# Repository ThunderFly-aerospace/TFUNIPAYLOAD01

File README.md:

# TFUNIPAYLOAD01 - universal interface for sensor payload 

Reference design of PX4 interface for generic [TF-ATMON](https://docs.thunderfly.cz/instruments/TF-ATMON) compatible payload. The purpose of this design is to connect a sensor to the [TF-ATMON](https://www.thunderfly.cz/tf-atmon.html) system, despite that the sensor does not have any driver in the flight stack (autopilot firmware), but at the same time, it is required for atmospheric measurement.

The sensor is connected to the TFUNIPAYLOAD board using a UART, I2C, GPIO, ADC, or SPI interface. 
ATmega in TFUNIPAYLOAD01 runs the Arduino firmware, which prepares [MAVLink](https://en.wikipedia.org/wiki/MAVLink) messages to be logged and transported to GCS running TF-ATMON infrastructure described in the block schematics. 

## Example of use

FMU firmware (PX4 or Ardupilot, for example) is capable of logging MAVLink data from the UART (Telemetry Port).  Therefore, the “UART Peripheral” connector on TFUNIPAYLOAD01 is intended for connecting a UART-based FMU using the Pixhawk DS-009 telemetry pinout. Typical devices include flight controllers (autopilot) or companion computers.

[Pixhawk standard connector pinout](https://github.com/pixhawk/Pixhawk-Standards/blob/master/DS-009%20Pixhawk%20Connector%20Standard.pdf) is as follows:

| Pin        | Signal | Voltage levels  | Read/Write | Write |
| ---------- |:------:| ---------------:|------|------|
| 1 (red)    | Vcc | +5V | Optional | Optional |
| 2 (blk)    | TX (OUT)  |   +3.3 V | PX4 -> Payload | -- |
| 3 (blk)    | RX (IN)   |   +3.3 V | Payload -> PX4 | Payload -> PX4 |
| 4 (blk)    | CTS (IN)  |   +3.3 V | -- | -- |
| 5 (blk)    | RTS (OUT) |   +3.3 V | -- | -- |
| 6 (blk)    | GND       |   GND    | GND | GND |

For data to be received by the PX4 autopilot, it must have a specific form. Explicitly, it needs to use a serial link with  [MAVLink v2](https://mavlink.io/en/) packets. In that case, the [Tunnel (#385)](https://mavlink.io/en/messages/common.html#TUNNEL) packets will be stored in the autopilot's log file and forwarded to the GCS. 
The [TFUSBSERIAL01](https://github.com/ThunderFly-aerospace/TFUSBSERIAL01) hardware could be used to easily check for correct wiring. 

The following library [c_library_v2](https://github.com/mavlink/c_library_v2), which is automatically generated from message definition files, could be used. 

## Firmware examples

There are multiple Arduino-based firmware examples for different use cases. 

#### TFUNIPAYLOAD

[TFUNIPAYLOAD.ino](/SW/arduino/src/TFUNIPAYLOAD/TFUNIPAYLOAD.ino) contains a basic example, which listens to MAVLink messages from the autopilot and sends tunnel packets with random data to the autopilot.

#### TFUNIPAYLOAD_MINIMAL

Since message parsing requires a lot of memory, we have prepared an example where only [HEARTBEAT](https://mavlink.io/en/messages/common.html#HEARTBEAT) and [TUNNEL](https://mavlink.io/en/messages/common.html#TUNNEL) messages are sent. This example does not require a connected TX (from autopilot), and it is, therefore, suitable for MCUs with less memory.

Source code: [TFUNIPAYLOAD_MINIMAL.ino](/SW/arduino/src/TFUNIPAYLOAD_MINIMAL/TFUNIPAYLOAD_MINIMAL.ino)

#### Tunnel packet sending function

[Tunnel packet sending function](https://github.com/ThunderFly-aerospace/TFUNIPAYLOAD/blob/79eee22fe32725179d1df2b6ca72e901e2be1834/SW/arduino/src/TFUNIPAYLOAD/TFUNIPAYLOAD.ino#L50) ```  mav.SendTunnelData(data, sizeof(data), 0, 1, 0); ``` is the main function that enables sending tunnel data to the autopilot. It takes the following as its arguments:
 * data in uint8_t [127] format
 * data length
 * data type (every type of logged data will have its ID - it serves for easy differentiation of different sensors
 * target sysid
 * target compid

If the data only needs to be logged, the target sysid and compid must match the autopilot’s address, which is usually `sysid: 1, compid: 1`. If the data has to be logged and sent to GCS, broadcast must be set: `sysid: 1, compid: 0` or better `sysid: 0, compid: 0`. 

The autopilot only has a limited amount of storage memory (SD card), and it is therefore necessary to ensure, on the payload’s side, that it does not fill up during the flight. Alternatively, a maximum bandwidth on the MAVLink interface can be set in the autopilot. It is not tested what happens when the level set is exceeded[2021/09]. 

## Autopilot configuration

In the autopilot’s PX4 firmware, it is necessary to correctly set the following parameters (MAV_1_FORWARD and others will be visible only after setting the parameter MAV_1_CONFIG and rebooting the PX4): 

|     Parametr    | Value | Description |
|-----------------|-----------|------|
| [MAV_1_CONFIG](http://docs.px4.io/main/en/advanced_config/parameter_reference.html#mavlink)    | TELEM 2   | The port on which MAVLink packets will be expected. Any free TELEM port can be set |
| [MAV_1_FORWARD](http://docs.px4.io/main/en/advanced_config/parameter_reference.html#mavlink)   | **1**     | Enable message forwarding from this port|
| [MAV_1_RADIO_CTL](http://docs.px4.io/main/en/advanced_config/parameter_reference.html#mavlink) | **0**     | |
| [MAV_1_RATE](http://docs.px4.io/main/en/advanced_config/parameter_reference.html#mavlink)      | **0 B/s** | |
| [SER_TEL2_BAUD](http://docs.px4.io/main/en/advanced_config/parameter_reference.html#serial)   |     57600 | It is necessary to configure the port that is set in `MAV_1_CONFIG` parameter. The setting of the baud rate port. |

How to set the parameters in PX4 is described in [manual](http://docs.px4.io/master/en/advanced_config/parameters.html#changing-a-parameter).

## How to check that the autopilot correctly receives MAVLink messages?

There are several options to find out whether the message sending is working correctly.

### Using the QGC

The message can be easily viewed live in [QGC](https://github.com/mavlink/qgroundcontrol/releases). For this procedure to function, two conditions must be fulfilled.

 1. The message must be broadcast, meaning the message must have set its target sysid and compid to 0, 0.
 2. The computer must be connected via a MAVLink instance that supports message forwarding (e.g., via TELEM1 port using modem or UART-USB converter); autopilot's USB does not support it.

 > Warning: this procedure will not work if the autopilot is connected via a USB cable to the Pixhawk's USB port.

After opening QGC, connect the autopilot to the computer (via RF modem or an external USB converter connected to the serial port). Once the autopilot is connected, live data (such as autopilot attitude) will become visible. A subsequent click on the QGC logo in the top left corner will open a menu where you select `Analyze tools` and then open `MAVLink inspector` in order to see a list of all messages. 

The list of messages, when functioning correctly, should contain TUNNEL messages. 

### Using the MAVLink PX4 console

An advantage of connecting via [PX4 console](https://docs.px4.io/main/en/debug/consoles.html) lies in its independence from broadcasting settings and the possibility of checking whether the message is received and parsed by the autopilot. If the message is visible here (and the logging is enabled), it is at the same time already logged. With this procedure, a USB cable connection to the autopilot can be used. 

Autopilot console can be entered using the following Python [script](https://github.com/ThunderFly-aerospace/PX4Firmware/blob/master/Tools/mavlink_shell.py) or using [QGC](https://github.com/mavlink/qgroundcontrol/releases).

 * In the case of using a Python script, it is enough to run the python3 script with a parameter of the chosen serial link to which the autopilot/modem is connected.
 * In the case of using QGC, the QGC must be opened in the autopilot console by clicking on the QGC logo (on the top), choosing `Analyze tools`, and choosing a console.

The received message can then be retrieved using the following command:

`listener mavlink_tunnel`

The command displays the current tunnel message. Adding the -n 100` parameter will cause a listing of 100 messages (and the new message will display by itself).

If the communication is working properly, the output should look like this:

### From a uLog file

The tunnel message can be logged into autopilot in a standard [uLog format](https://docs.px4.io/main/en/dev_log/ulog_file_format.html). However, because tools like [Flight review](https://review.px4.io/) are unable to display such data format, it is necessary to overcome this problem using a suitable tool. One option is using the [PlotJuggler](https://plotjuggler.io/). 
Another possibility for opening the log is the [Jupiter notebook](https://github.com/ThunderFly-aerospace/TFUNIPAYLOAD/blob/master/SW/LogViewer/ReadTunnelData.ipynb).

## Known limitations

  * Avoiding overloading the autopilot's memory with messages must be ensured on the payload side
  * A maximum of 2 devices + modem or 3 devices without a modem can be connected in this way. The limitation is caused by the MAVLink driver, which is only able to connect a maximum of 3 instances of MAVLink devices, and also due to the limited number of UART interfaces of the autopilot.
  * It is not possible for the input of payload messages and output to [sik modem](https://github.com/ThunderFly-aerospace/TFSIK01) to have the same type of MAVLink messages (stream) that would differ only in the number of messages per second. This means that it is not possible to simply select a data stream to be transmitted to the ground from the data stream intended for logging. If it is necessary to log more detailed data (with higher frequency) another MAVLink message must be logged.

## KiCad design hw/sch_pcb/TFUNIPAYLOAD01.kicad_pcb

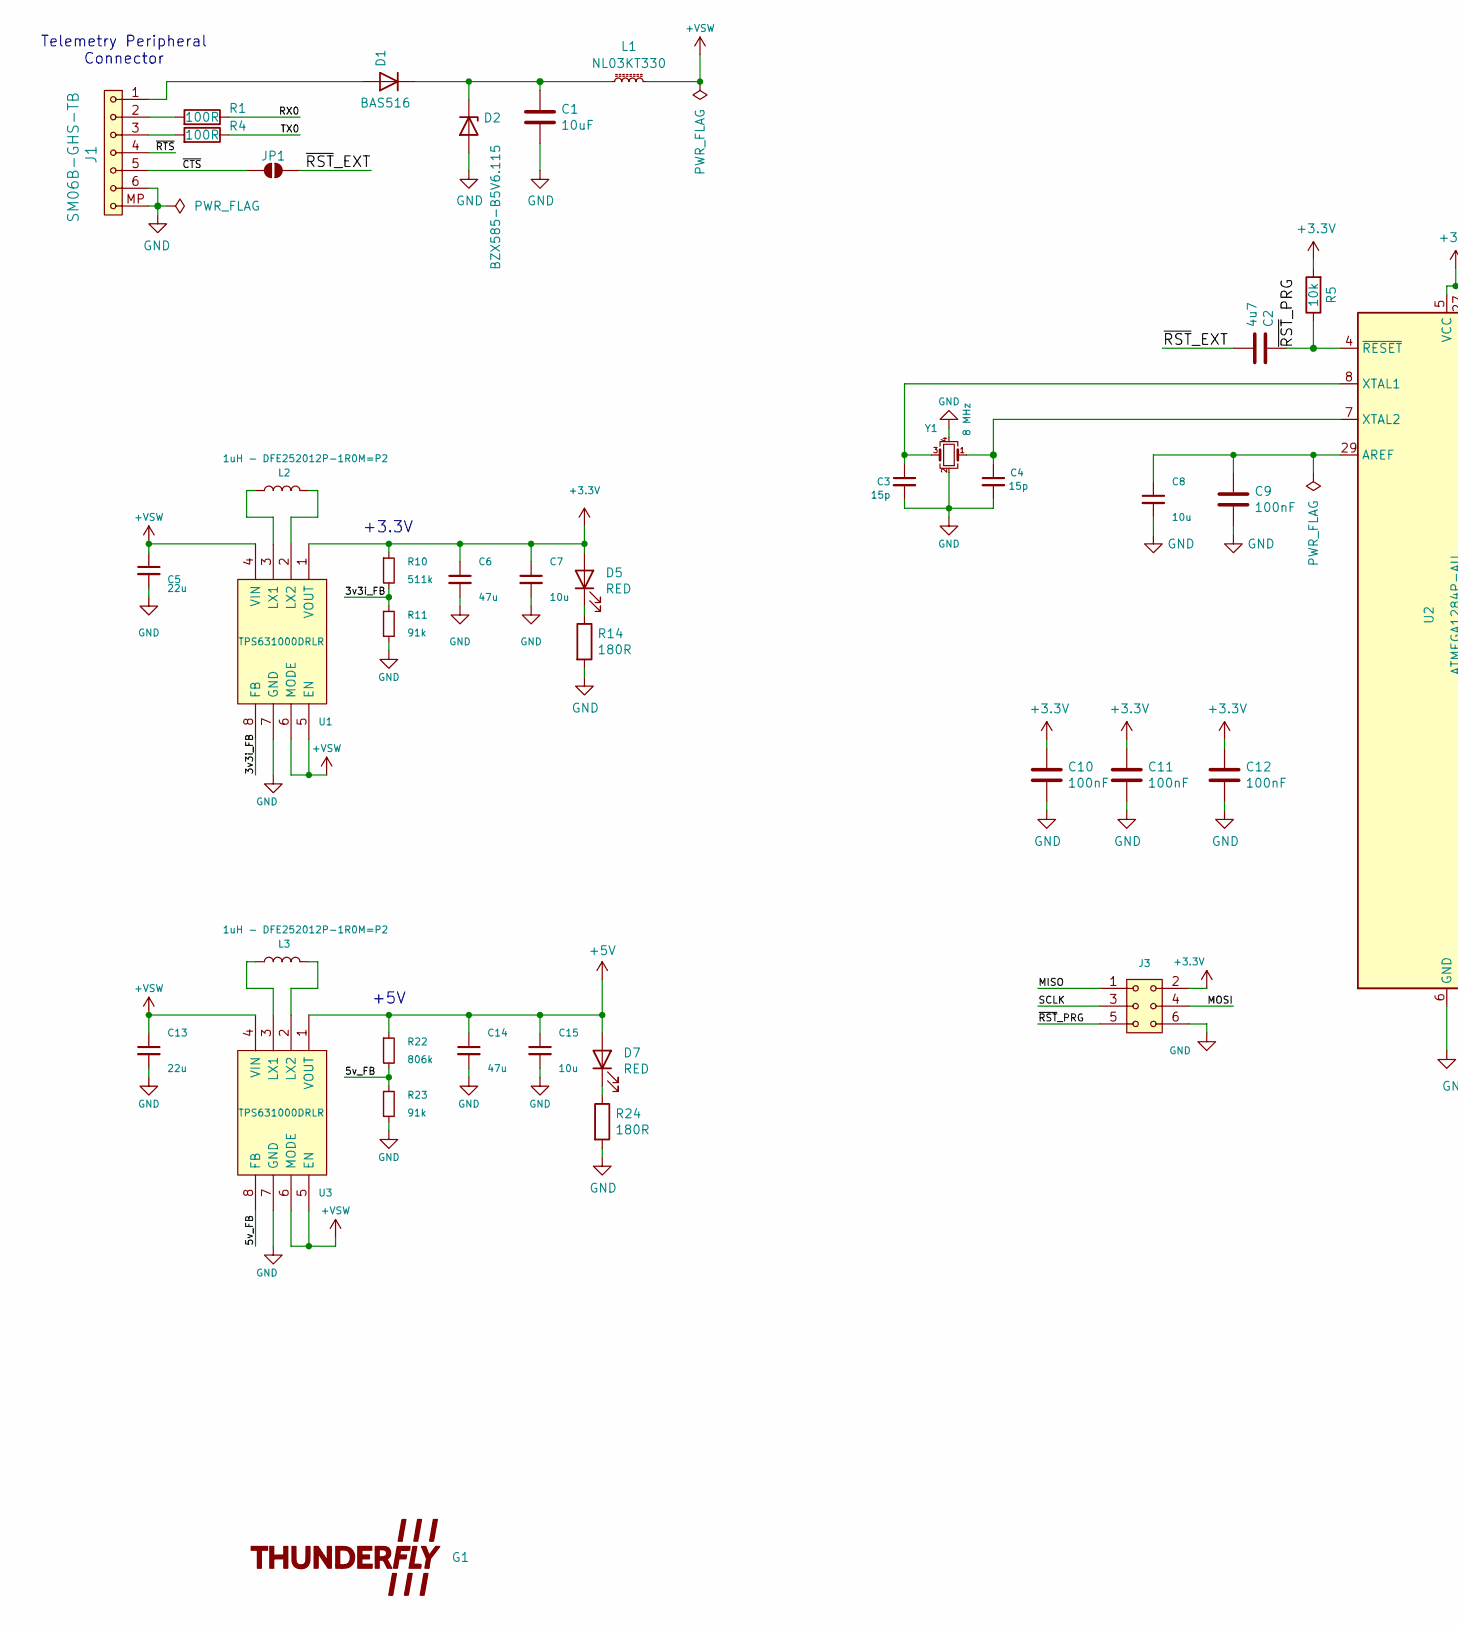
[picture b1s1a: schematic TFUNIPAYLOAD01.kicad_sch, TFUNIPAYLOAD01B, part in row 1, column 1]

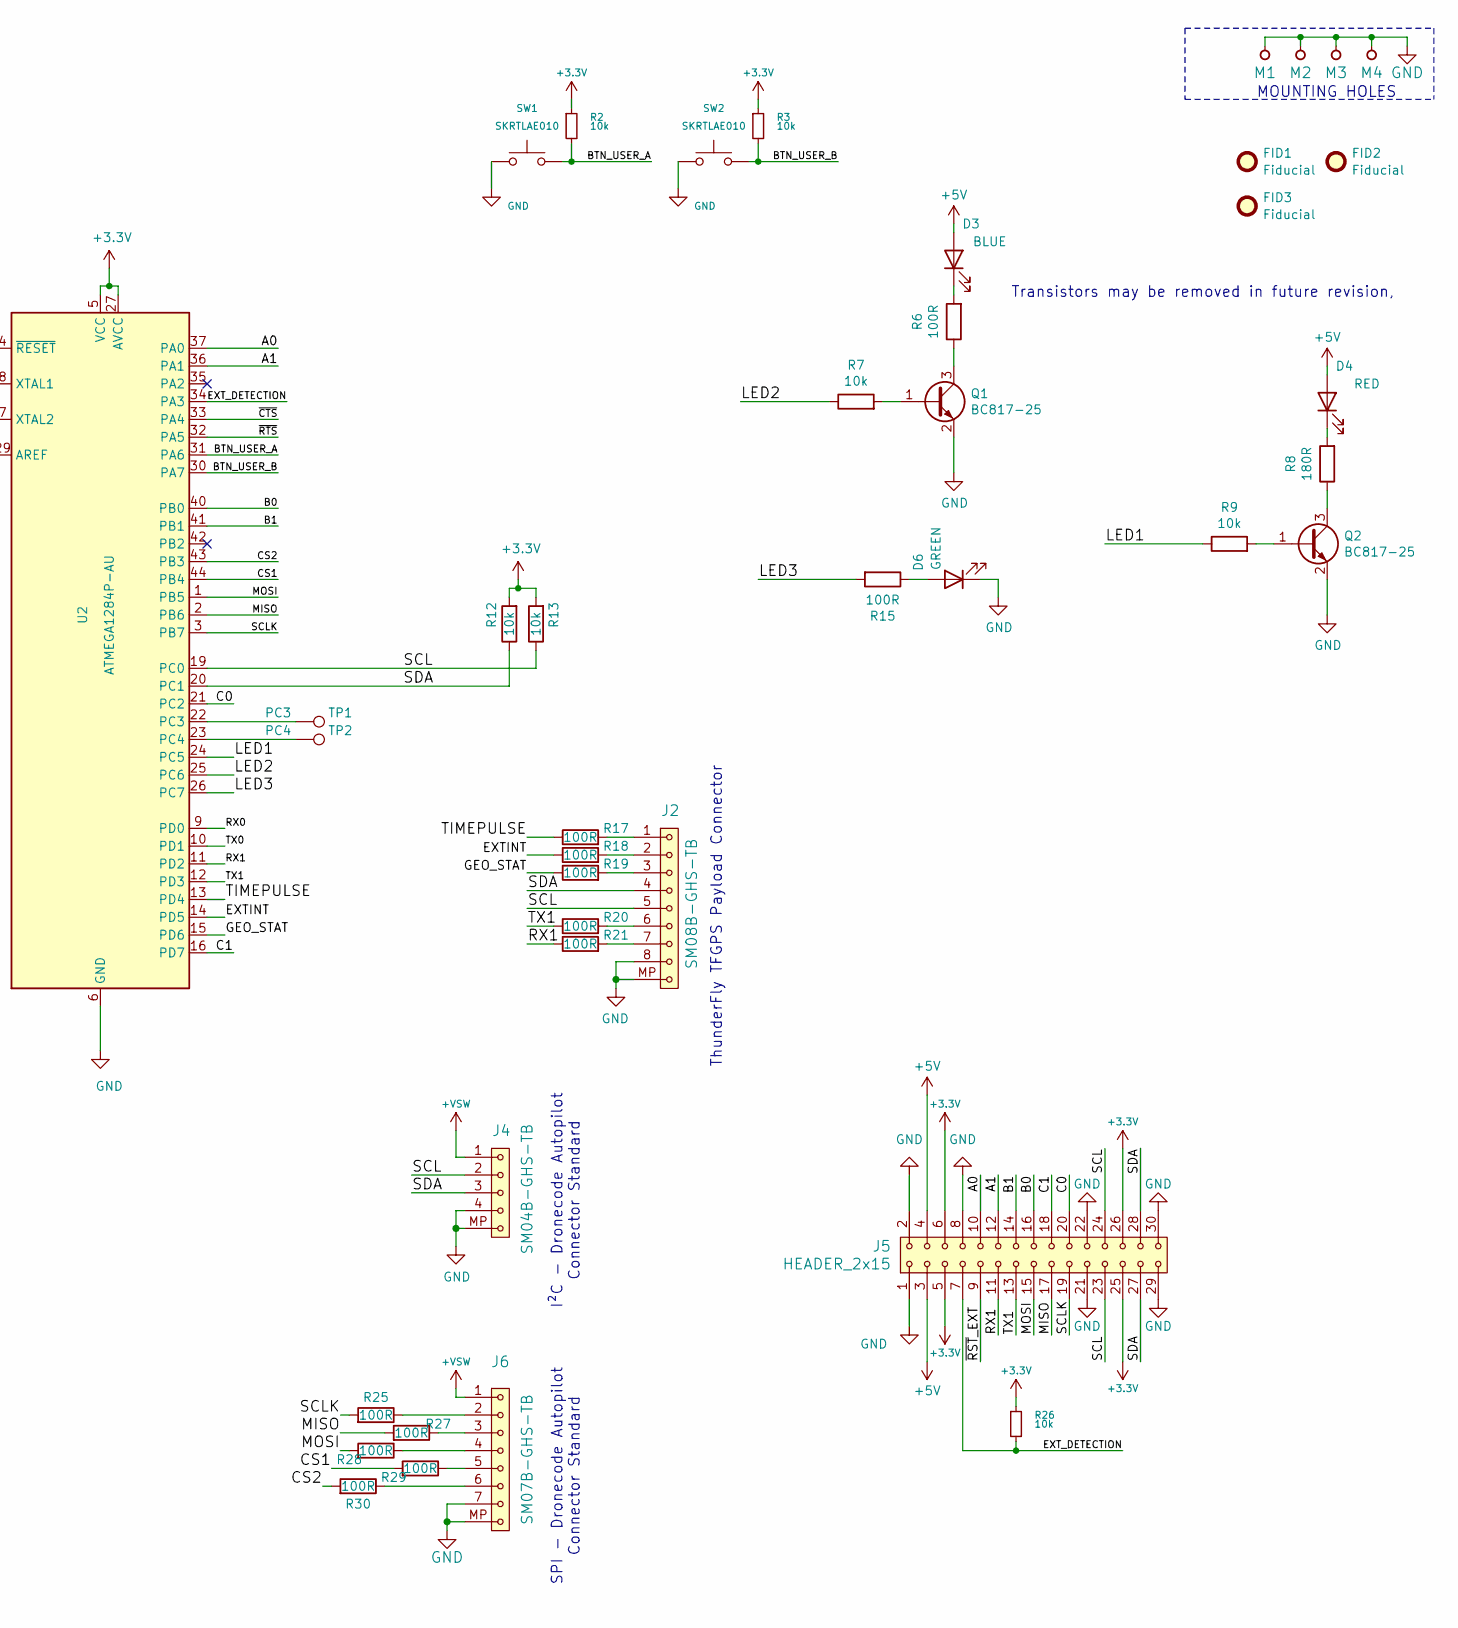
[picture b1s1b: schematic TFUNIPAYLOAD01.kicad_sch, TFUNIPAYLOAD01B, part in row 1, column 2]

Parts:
C1: 10uF; C_0805_2012Metric
C2: 4u7; C_0805_2012Metric
C3, C4: 15p; C_0805_2012Metric
C5, C13: 22u; C_0805_2012Metric
C6, C14: 47u; C_0805_2012Metric
C7, C8, C15: 10u; C_0805_2012Metric
C9, C10, C11, C12: 100nF; C_0805_2012Metric
D1: BAS516; D_SOD-523
D2: BZX585-B5V6.115; D_SOD-523
D3: BLUE; LED_1206_mill
D4, D5, D7: RED; LED_1206_mill
D6: GREEN; LED_1206_mill
FID1, FID2, FID3: Fiducial; Fiducial_1mm_Mask2mm
G1: LOGO; TF
J1: SM06B-GHS-TB; JST_GH_SM06B-GHS-TB_1x06-1MP_P1.25mm_Horizontal
J2: SM08B-GHS-TB; JST_GH_SM08B-GHS-TB_1x08-1MP_P1.25mm_Horizontal
J3: HEADER_2x03; SMD_2x03_WO_paste
J4: SM04B-GHS-TB; JST_GH_SM04B-GHS-TB_1x04-1MP_P1.25mm_Horizontal
J5: HEADER_2x15; Straight_2x15
J6: SM07B-GHS-TB; JST_GH_SM07B-GHS-TB_1x07-1MP_P1.25mm_Horizontal
JP1: SolderJumper_2_Open; SolderJumper-2_P1.3mm_Open_RoundedPad1.0x1.5mm
L1: NL03KT330; L_0603_1608Metric_Pad1.05x0.95mm_HandSolder
L2, L3: 1uH - DFE252012P-1R0M=P2; L_1008_2520Metric
M1, M2, M3, M4: HOLE; MountingHole_3mm
Q1, Q2: BC817-25; SOT-23
R1, R4, R6, R15, R17, R18, R19, R20, R21, R25, R27, R28, R29, R30: 100R; R_0805_2012Metric
R2, R3, R5, R7, R9, R12, R13, R26: 10k; R_0805_2012Metric
R8, R14, R24: 180R; R_0805_2012Metric
R10: 511k; R_0805_2012Metric
R11, R23: 91k; R_0805_2012Metric
R22: 806k; R_0805_2012Metric
SW1, SW2: SKRTLAE010; KMT031 NGJ LHS C&K
TP1: PC3; TestPoint_Pad_D1.0mm
TP2: PC4; TestPoint_Pad_D1.0mm
U1, U3: TPS631000DRLR; SOT-583-8; Mouser Part Number 595-TPS631000DRLR
U2: ATMEGA1284P-AU; TQFP-44_10x10mm_P0.8mm
Y1: 8 MHz; Crystal_SMD_3225-4Pin_3.2x2.5mm

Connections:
+3.3V: C6.1, C7.1, C10.1, C11.1, C12.1, D5.2 (A), J3.2, J5.5, J5.6, J5.25, J5.26, R2.1, R3.1, R5.2, R10.1, R12.2, R13.2, R26.1, U1.1 (VOUT), U2.5 (VCC), U2.17 (VCC), U2.27 (AVCC), U2.38 (VCC)
+5V: C14.1, C15.1, D3.2 (A), D4.2 (A), D7.2 (A), J5.3, J5.4, R22.1, U3.1 (VOUT)
+VSW: C5.1, C13.1, J4.1, J6.1, L1.2, U1.4 (VIN), U1.5 (EN), U1.6 (MODE), U3.4 (VIN), U3.5 (EN), U3.6 (MODE)
/3v3i_FB: R10.2, R11.1, U1.8 (FB)
/5v_FB: R22.2, R23.1, U3.8 (FB)
/A0: J5.10, U2.37 (PA0)
/A1: J5.12, U2.36 (PA1)
/B0: J5.16, U2.40 (PB0)
/B1: J5.14, U2.41 (PB1)
/BTN_USER_A: R2.2, SW1.1, U2.31 (PA6)
/BTN_USER_B: R3.2, SW2.1, U2.30 (PA7)
/C0: J5.20, U2.21 (PC2)
/C1: J5.18, U2.16 (PD7)
/CS1: R29.2, U2.44 (PB4)
/CS2: R30.2, U2.43 (PB3)
/EXTINT: R18.1, U2.14 (PD5)
/EXT_DETECTION: J5.7, R26.2, U2.34 (PA3)
/GEO_STAT: R19.1, U2.15 (PD6)
/LED1: R9.1, U2.24 (PC5)
/LED2: R7.1, U2.25 (PC6)
/LED3: R15.2, U2.26 (PC7)
/MISO: J3.1, J5.17, R27.2, U2.2 (PB6)
/MOSI: J3.4, J5.15, R28.2, U2.1 (PB5)
/RX0: R1.1, U2.9 (PD0)
/RX1: J5.11, R21.1, U2.11 (PD2)
/SCL: J2.5, J4.2, J5.23, J5.24, R13.1, U2.19 (PC0)
/SCLK: J3.3, J5.19, R25.2, U2.3 (PB7)
/SDA: J2.4, J4.3, J5.27, J5.28, R12.1, U2.20 (PC1)
/TIMEPULSE: R17.1, U2.13 (PD4)
/TX0: R4.1, U2.10 (PD1)
/TX1: J5.13, R20.1, U2.12 (PD3)
/~CTS: J1.5, JP1.2 (B), U2.33 (PA4)
/~RST_EXT: C2.2, J5.9, JP1.1 (A)
/~RST_PRG: C2.1, J3.5, R5.1, U2.4 (~RESET)
/~RTS: J1.4, U2.32 (PA5)
GND: C1.2, C3.2, C4.2, C5.2, C6.2, C7.2, C8.2, C9.2, C10.2, C11.2, C12.2, C13.2, C14.2, C15.2, D2.2 (A), D6.1 (K), J1.6, J1.MP, J2.8, J2.MP, J3.6, J4.4, J4.MP, J5.1, J5.2, J5.8, J5.21, J5.22, J5.29, J5.30, J6.7, J6.MP, M1.1, M2.1, M3.1, M4.1, Q1.2 (E), Q2.2 (E), R11.2, R14.2, R23.2, R24.2, SW1.2, SW2.2, U1.7 (GND), U2.6 (GND), U2.18 (GND), U2.28 (GND), U2.39 (GND), U3.7 (GND), Y1.2, Y1.4
unnamed: D1.2 (A), J1.1
unnamed: C1.1, D1.1 (K), D2.1 (K), L1.1
unnamed: D3.1 (K), R6.2
unnamed: D4.1 (K), R8.2
unnamed: D5.1 (K), R14.1
unnamed: D6.2 (A), R15.1
unnamed: D7.1 (K), R24.1
unnamed: J1.2, R1.2
unnamed: J1.3, R4.2
unnamed: J2.1, R17.2
unnamed: J2.2, R18.2
unnamed: J2.3, R19.2
unnamed: J2.6, R20.2
unnamed: J2.7, R21.2
unnamed: J6.2, R25.1
unnamed: J6.3, R27.1
unnamed: J6.4, R28.1
unnamed: J6.5, R29.1
unnamed: J6.6, R30.1
unnamed: Q1.1 (B), R7.2
unnamed: Q1.3 (C), R6.1
unnamed: Q2.1 (B), R9.2
unnamed: Q2.3 (C), R8.1
unnamed: L2.1, U1.3 (LX1)
unnamed: L2.2, U1.2 (LX2)
unnamed: C8.1, C9.1, U2.29 (AREF)
unnamed: TP1.1, U2.22 (PC3)
unnamed: TP2.1, U2.23 (PC4)
unnamed: C3.1, U2.8 (XTAL1), Y1.3
unnamed: C4.1, U2.7 (XTAL2), Y1.1
unnamed: L3.1, U3.3 (LX1)
unnamed: L3.2, U3.2 (LX2)

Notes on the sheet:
I²C - Dronecode Autopilot Connector Standard
Transistors may be removed in future revision,
SPI - Dronecode Autopilot Connector Standard
ThunderFly TFGPS Payload Connector
Telemetry Peripheral Connector
+5V
+3.3V
MOUNTING HOLES

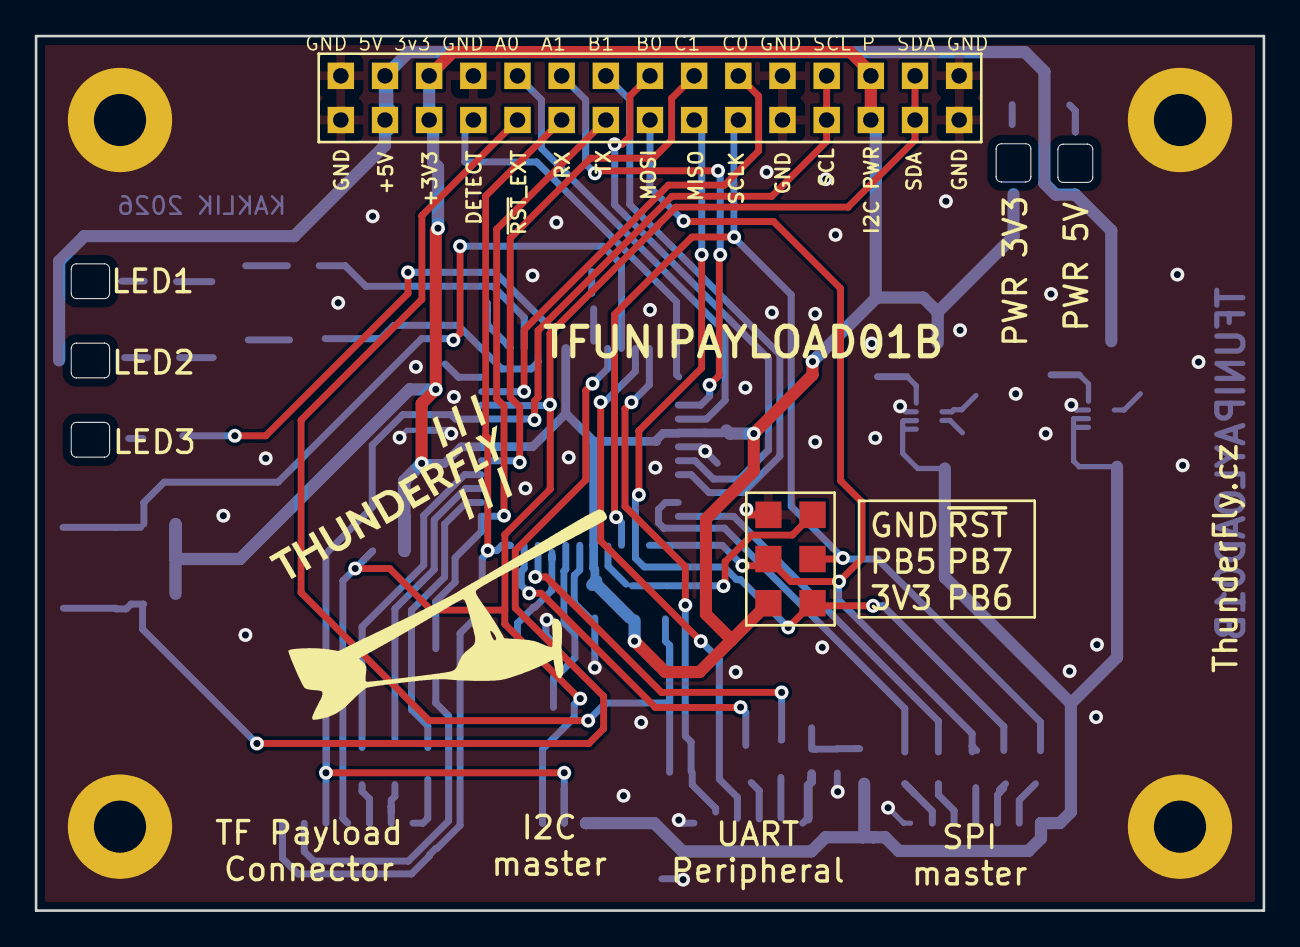
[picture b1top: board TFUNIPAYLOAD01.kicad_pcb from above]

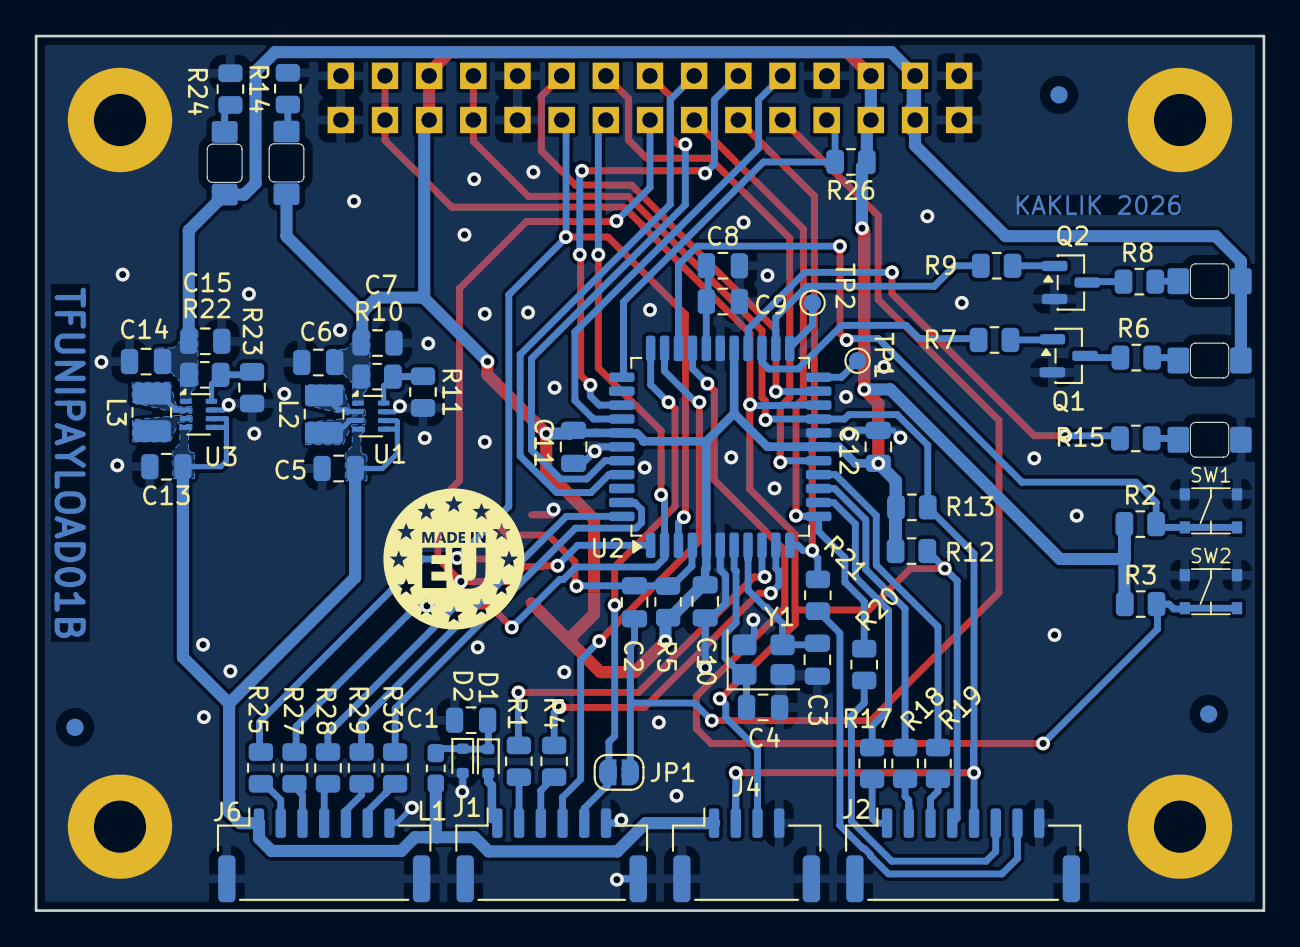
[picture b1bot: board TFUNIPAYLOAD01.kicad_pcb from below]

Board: 2 copper layers, 70.6 x 50.3 mm, 79 parts (72 on the bottom side), 68 nets.

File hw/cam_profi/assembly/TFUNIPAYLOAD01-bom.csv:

Component,Description,Part,References,Value,Footprint,Quantity Per PCB,Datasheet,ust_id,sim.device,sim.pins,height,mouser part number,mouser price/stock,manufacturer_name,manufacturer_part_number
1,"Unpolarized capacitor, small symbol",C_Small,C3C4,15p,C_0805_2012Metric,2,~,5c70984712875079b91f8b32,,,,,,,
2,Unpolarized capacitor,C,C9C10C11C12,100nF,C_0805_2012Metric,4,~,6508260b462c6d9e720541f1 5c70984712875079b91f8b4c,,,,,,,
3,Unpolarized capacitor,C,C2,4u7,C_0805_2012Metric,1,~,5e3ff8fc1287502a33bad7a3,,,,,,,
4,Unpolarized capacitor,C,C1C7C8C15,10uF,C_0805_2012Metric,4,~,5c70984712875079b91f8b53,,,,,,,
5,"Unpolarized capacitor, small symbol",C_Small,C5C13,22u,C_0805_2012Metric,2,~,650b58f1462c6d9e7205463b,,,,,,,
6,"Unpolarized capacitor, small symbol",C_Small,C6C14,47u,C_0805_2012Metric,2,~,5c70984812875079b91f8bbf,,,,,,,
7,"100V, 0.25A, High-speed Switching Diode, SOD-523",BAS516,D1,BAS516,D_SOD-523,1,https://assets.nexperia.com/documents/data-sheet/BAS16_SER.pdf,693421c6ea235ce78ba25972,D,1=K 2=A,,,,,
8,Light emitting diode,LED,D3,BLUE,LED_1206_mill,1,~,5c70984512875079b91f8898,,,,,,,
9,Zener diode,D_Zener,D2,BZX585-B5V6.115,D_SOD-523,1,https://www.tme.eu/Document/7f59fc987b8fce7e4ab18399d6e66bd1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,60879d38128750769ee58e48,,,,,,,
10,Light emitting diode,LED,D6,GREEN,LED_1206_mill,1,~,5c70984412875079b91f8895,,,,,,,
11,Light emitting diode,LED,D4D5D7,RED,LED_1206_mill,3,~,5c70984412875079b91f8896,,,,,,,
12,2x15 2.54 mm pitch header,HEADER_2x15,J5,HEADER_2x15,Straight_2x15,1,,68226dbfee7fc534862c67d1,,,,,,,
13,,SM04B-GHS-TB,J4,SM04B-GHS-TB,JST_GH_SM04B-GHS-TB_1x04-1MP_P1.25mm_Horizontal,1,,5c86273d1287500b4e0280be,,,,,,,
14,1x07 2.54 mm pitch header,SM06B-GHS-TB,J1,SM06B-GHS-TB,JST_GH_SM06B-GHS-TB_1x06-1MP_P1.25mm_Horizontal,1,,5fa0f70212875025b3977932,,,,,,,
15,1x08 2.54 mm pitch header,SM07B-GHS-TB,J6,SM07B-GHS-TB,JST_GH_SM07B-GHS-TB_1x07-1MP_P1.25mm_Horizontal,1,,5c7250081287500b4e112e78,,,,,,,
16,1x08 2.54 mm pitch header,SM08B-GHS-TB,J2,SM08B-GHS-TB,JST_GH_SM08B-GHS-TB_1x08-1MP_P1.25mm_Horizontal,1,,5fa0f75012875025b3977948,,,,,,,
17,Inductor,L,L2L3,1uH - DFE252012P-1R0M=P2,L_1008_2520Metric,2,~,650b5977462c6d9e72054656,,,,,,,
18,"Inductor with ferrite core, small symbol",L_Ferrite_Small,L1,NL03KT330,L_0603_1608Metric_Pad1.05x0.95mm_HandSolder,1,~,64fe1808f3b9d36f37fc944d,,,,,,,
19,"0.8A Ic, 45V Vce, NPN Transistor, SOT-23",BC817,Q1Q2,BC817-25,SOT-23,2,~,5c70984712875079b91f8aea,,,,,,,
20,Resistor,R,R15,18R,R_0805_2012Metric,1,~,5c70984512875079b91f896e,,,,,,,
21,Resistor,R,R6,51R,R_0805_2012Metric,1,~,5c70984512875079b91f8953,,,,,,,
22,Resistor,R,R8,82R,R_0805_2012Metric,1,~,5c70984512875079b91f8976,,,,,,,
23,Resistor,R,R1R4R17R18R19R20R21R25R27R28R29R30,100R,R_0805_2012Metric,12,~,5c70984512875079b91f8977 5c70984512875079b91f8956,,,,,,,
24,Resistor,R,R14R24,180R,R_0805_2012Metric,2,~,5c70984512875079b91f897c,,,,,,,
25,"Resistor, small symbol",R_Small,R2R3R5R7R9R12R13R26,10k,R_0805_2012Metric,8,~,5c70984612875079b91f899f 5c70984512875079b91f8962,,,,,,,
26,"Resistor, small symbol",R_Small,R11R23,91k,R_0805_2012Metric,2,~,5c70984712875079b91f8a95,,,,,,,
27,"Resistor, small symbol",R_Small,R10,511k,R_0805_2012Metric,1,~,650b5a43462c6d9e7205468e,,,,,,,
28,"Resistor, small symbol",R_Small,R22,806k,R_0805_2012Metric,1,~,650b5abb462c6d9e720546b8,,,,,,,
29,"Push button switch, generic, two pins",SW_Push,SW1SW2,SKRTLAE010,KMT031 NGJ LHS C&K,2,~,612515a61287500165a9771d,,,,,,,
30,"20MHz, 128kB Flash, 16kB SRAM, 4kB EEPROM, JTAG, TQFP-44",ATmega1284P-A,U2,ATMEGA1284P-AU,TQFP-44_10x10mm_P0.8mm,1,http://www.atmel.com/Images/Atmel-8272-8-bit-AVR-microcontro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,5c70984412875079b91f888e,,,,,,,
31,"Switching Voltage Regulators 1.5-A output current, high power density buck-boost converter",TPS631000DRLR,U1U3,TPS631000DRLR,SOT-583-8,2,https://www.ti.com/lit/ds/symlink/tps631000.pdf?ts=1652152702265,63de5ae4ae0b2d5aa05e2714,,,0.5,595-TPS631000DRLR,https://www.mouser.co.uk/ProductDetail/Texas-Instruments/TPS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,Texas Instruments,TPS631000DRLR
32,"Four pin crystal, GND on pins 2 and 4, small symbol",Crystal_GND24_Small,Y1,8 MHz,Crystal_SMD_3225-4Pin_3.2x2.5mm,1,~,65481c4c462c6d9e72056ac8,,,,,,,

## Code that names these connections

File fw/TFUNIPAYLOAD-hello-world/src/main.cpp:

/*
  TFUNIPAYLOAD01B
  ATmega1284P @ 8 MHz (external oscillator)

                     Mighty 1284p
                      +---\/---+
           (D 0) PB0 1|        |40 PA0 (AI 0 / D24)
           (D 1) PB1 2|        |39 PA1 (AI 1 / D25)
      INT2 (D 2) PB2 3|        |38 PA2 (AI 2 / D26)
       PWM (D 3) PB3 4|        |37 PA3 (AI 3 / D27)
    PWM/SS (D 4) PB4 5|        |36 PA4 (AI 4 / D28)
      MOSI (D 5) PB5 6|        |35 PA5 (AI 5 / D29)
  PWM/MISO (D 6) PB6 7|        |34 PA6 (AI 6 / D30)
   PWM/SCK (D 7) PB7 8|        |33 PA7 (AI 7 / D31)
                 RST 9|        |32 AREF
                VCC 10|        |31 GND
                GND 11|        |30 AVCC
              XTAL2 12|        |29 PC7 (D 23)
              XTAL1 13|        |28 PC6 (D 22)
      RX0 (D 8) PD0 14|        |27 PC5 (D 21) TDI
      TX0 (D 9) PD1 15|        |26 PC4 (D 20) TDO
RX1/INT0 (D 10) PD2 16|        |25 PC3 (D 19) TMS
TX1/INT1 (D 11) PD3 17|        |24 PC2 (D 18) TCK
     PWM (D 12) PD4 18|        |23 PC1 (D 17) SDA
     PWM (D 13) PD5 19|        |22 PC0 (D 16) SCL
     PWM (D 14) PD6 20|        |21 PD7 (D 15) PWM
                      +--------+
*/

#include <Arduino.h>

#if !defined(PIN_LED_RED) || !defined(PIN_LED_BLUE) || !defined(PIN_LED_GREEN) || !defined(PIN_BTN_USER_A) || !defined(PIN_BTN_USER_B)
#error "Board macros PIN_LED_* and PIN_BTN_USER_* must be provided by board configuration"
#endif

static bool phase = false;
static uint32_t counter = 0;
static uint32_t lastBlinkToggleMs = 0;

void setup()
{
  Serial.begin(115200);

  pinMode(PIN_LED_RED, OUTPUT);
  pinMode(PIN_LED_BLUE, OUTPUT);
  pinMode(PIN_LED_GREEN, OUTPUT);

  // Buttons have external pull-up resistors and are active in LOW state.
  pinMode(PIN_BTN_USER_A, INPUT);
  pinMode(PIN_BTN_USER_B, INPUT);

  digitalWrite(PIN_LED_GREEN, LOW);
  digitalWrite(PIN_LED_BLUE, HIGH);
  digitalWrite(PIN_LED_RED, HIGH);

  lastBlinkToggleMs = millis();

  Serial.println("TFUNIPAYLOAD01 hello-world");
}

void loop()
{
  const bool btnAIsPressed = digitalRead(PIN_BTN_USER_A) == LOW;
  const bool btnBIsPressed = digitalRead(PIN_BTN_USER_B) == LOW;

  uint16_t blinkDelayMs = 500;
  if (btnAIsPressed && btnBIsPressed) {
    blinkDelayMs = 80;
  } else if (btnAIsPressed) {
    blinkDelayMs = 150;
  } else if (btnBIsPressed) {
    blinkDelayMs = 1000;
  }

  const bool anyButtonIsPressed = btnAIsPressed || btnBIsPressed;

  digitalWrite(PIN_LED_RED, anyButtonIsPressed);

  const uint32_t nowMs = millis();
  if (nowMs - lastBlinkToggleMs >= blinkDelayMs) {
    lastBlinkToggleMs = nowMs;
    phase = !phase;

    digitalWrite(PIN_LED_GREEN, phase ? HIGH : LOW);
    digitalWrite(PIN_LED_BLUE, phase ? LOW : HIGH);

    counter++;
    Serial.print("line=");
    Serial.print(counter);
    Serial.print(" uptime=");
    Serial.print(millis() / 1000UL);
    Serial.print("s btnA=");
    Serial.print(btnAIsPressed ? "pressed" : "released");
    Serial.print(" btnB=");
    Serial.print(btnBIsPressed ? "pressed" : "released");
    Serial.print(" blink=");
    Serial.print(blinkDelayMs);
    Serial.println("ms");
  }
}

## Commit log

2020-10-23 initial version of mavlink sender
2020-10-23 Create LICENSE
2020-11-17 minimal version of example
2020-11-17 add log viewer
2020-11-17 Fix links syntax
2020-11-18 Add section about system limitations.
2021-02-04 Add block schematics to the readme.
2021-09-05 pridat tabulku se seznamem zarizeni, upresneni mavid sysid
2022-11-12 Partially translated readme
2022-11-16 Add a link to uLog description.
2022-11-24 Translation
2022-11-24 Translate
2022-11-26 Clarify the sentence. Rewording.
2022-11-28 Fix inaccuracies
2023-09-30 Update README.md
    Add a link to TFUSBSERIAL01.
2023-12-30 Update README.md
    Generic information about supported TF-ATMON sensors is moved to the https://github.com/ThunderFly-aerospace/TF-ATMON repository.
2025-06-21 Add mlab module hardware as submodule.
2025-11-18 Initial schematics. #2 WIP
2025-11-24 Fix submodule path.
2025-11-24 Update workflow files
2025-11-25 Update schematics. Resolve #2
2025-11-25 Update actions products
2025-11-25 Fix ERC errors. Fix #3.
2025-12-27 PCB layout WIP.
2025-12-27 Components placement.
2025-12-27 Footprints updated.
2025-12-27 Routing.
2025-12-27 Pinheader correctly positioned.
2025-12-28 Pinheader changed to footprint with square pads. Routing more nets.
2025-12-28 Routed PCB.
2025-12-29 Improve layout.
2025-12-29 Improve readme.
2026-01-07 Improve layout and graphics.
2026-01-09 Improve silkscreen.
2026-01-20 Improve connector description.
2026-01-21 Create dimensioned drawings.
2026-01-25 Adding Made in EU symbol.
2026-02-11 Add github actions definition to build firmware.
2026-02-11 Fix workflow.
2026-02-13 Update and cleanup submodules.
2026-02-13 Fix firmware workflow bootstrap and MAVLink dependency
2026-02-13 Run firmware build on pull requests
2026-02-13 Fix firmware include path and disable KiCad auto-commit in PR branches
2026-02-13 Run KiCad workflow on PRs without repo write-back
2026-02-13 Fix MAVLink bootstrap when c_library_v2 directory exists but is empty
2026-02-13 Use recursive submodule checkout for firmware CI instead of MAVLink-specific clone
2026-02-13 Initialize only firmware submodules in CI checkout
2026-02-13 Remove custom submodule init step and use checkout submodules
2026-02-13 Use PAT token in firmware workflow checkout for submodule access
2026-02-13 Fix firmware workflow paths after compile to avoid wrong working directory
2026-02-13 Fix firmware workflow paths after compile to avoid wrong working directory, extended build
2026-02-13 Fix firmware workflow paths after compile to avoid wrong working directory, extended build, extended build
2026-02-13 Fix firmware workflow paths after compile to avoid wrong working directory, extended build, extended build, extended build
2026-02-13 Fix firmware workflow paths after compile to avoid wrong working directory, extended build, extended build, extended build, extended build
2026-02-13 Fix firmware workflow paths after compile to avoid wrong working directory, extended build, extended build, extended build, extended build, extended build
2026-02-13 Fix firmware workflow paths after compile to avoid wrong working directory, extended build, extended build, extended build, extended build, extended build, extended build
2026-02-13 Fix firmware workflow paths after compile to avoid wrong working directory, extended build, extended build, extended build, extended build, extended build, extended build, extended build
2026-02-13 Fix firmware workflow paths after compile to avoid wrong working directory, extended build, extended build, extended build, extended build, extended build, extended build, extended build, extended bu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
2026-02-13 Fix firmware workflow paths after compile to avoid wrong working directory, extended build, extended build, extended build, extended build, extended build, extended build, extended build, extended bu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
2026-02-13 Fix firmware workflow paths after compile to avoid wrong working directory, extended build, extended build, extended build, extended build, extended build, extended build, extended build, extended bu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
2026-02-13 Fix firmware workflow paths after compile to avoid wrong working directory, extended build, extended build, extended build, extended build, extended build, extended build, extended build, extended bu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
2026-02-13 move current arduino fw into platformIO projects
2026-02-13 Fix firmware build workflow
2026-02-13 Fix firmware build workflow, extended build
2026-02-13 Update build_fw.yml
    create build directory in SW/arduino/
2026-02-13 Update build_fw.yml, extended build
2026-02-13 Update build_fw.yml, extended build, extended build
2026-02-13 Cleanup unused files.
2026-02-13 Cleanup unused files., extended build
2026-02-14 Update workflow files, extended build
2026-02-14 Revert "Update workflow files"
    This reverts commit f3245563582849209978778c96b9f53fcb781f75.
2026-02-14 Update assets submodule.
2026-02-14 Update assets submodule., extended build
2026-02-14 Include TFUNIPAYLOAD-hello-world in PlatformIO firmware workflow
2026-02-14 Fix PlatformIO invocation in firmware workflow build step
2026-02-14 Modify workflow to adopt PlatformIO firmware CI build (#11)
    * Include TFUNIPAYLOAD-hello-world in PlatformIO firmware workflow
    * Fix PlatformIO invocation in firmware workflow build step
2026-02-14 Modify workflow to adopt PlatformIO firmware CI build (#11), extended build
2026-02-14 Modify workflow to adopt PlatformIO firmware CI build (#11), extended build, extended build
2026-02-14 Move build matrix to external config file fw/build_matrix.yaml
2026-02-14 Update build_fw.yml
    Exclude run-on change in fw/build
2026-02-14 Delete SW/arduino directory
    Sources moved to fw directory as platformIO projects.
2026-02-15 Automatic update of KiCAD outputs
2026-02-16 Fix cummulation of binaries in build directory.
2026-02-16 Fix cummulation of binaries in build directory., extended build
2026-02-16 Fix platformIO config.
2026-02-16 Fix platformIO config., extended build
2026-02-16 Unify PlatformIO board definition across firmware projects
2026-02-16 Fix PlatformIO shared boards_dir configuration
2026-02-16 Unify PlatformIO board definition across firmware projects (#13)
    Make PlatformIO board configuration shared across project directories.
2026-02-16 Unify PlatformIO board definition across firmware projects (#13), extended build
2026-02-16 Add definition of buttons and LEDs.
2026-02-16 Add definition of buttons and LEDs., extended build
2026-02-17 Add LED blinking.
2026-02-17 Add LED blinking., extended build
2026-02-17 Update build_fw.yml
    Fix rewriting build directory with old files.
2026-02-17 Share platformIO configfuration files as symlinks.
2026-02-17 Fix symlink absolute path, change to relative.
2026-02-17 Fix symlink absolute path, change to relative., extended build
2026-02-17 Configure bootloader LED.
2026-02-17 Configure bootloader LED., extended build
2026-03-02 Update wokflow by project-unified version from AIRDOS03.
2026-03-02 Update wokflow by project-unified version from AIRDOS03., extended build
2026-03-02 Fix LED resistors values.
2026-03-03 Fix red LED swith on in case any button pressed.
2026-03-03 Fix red LED swith on in case any button pressed., extended build
2026-03-23 Adding datasheet for MCU.
